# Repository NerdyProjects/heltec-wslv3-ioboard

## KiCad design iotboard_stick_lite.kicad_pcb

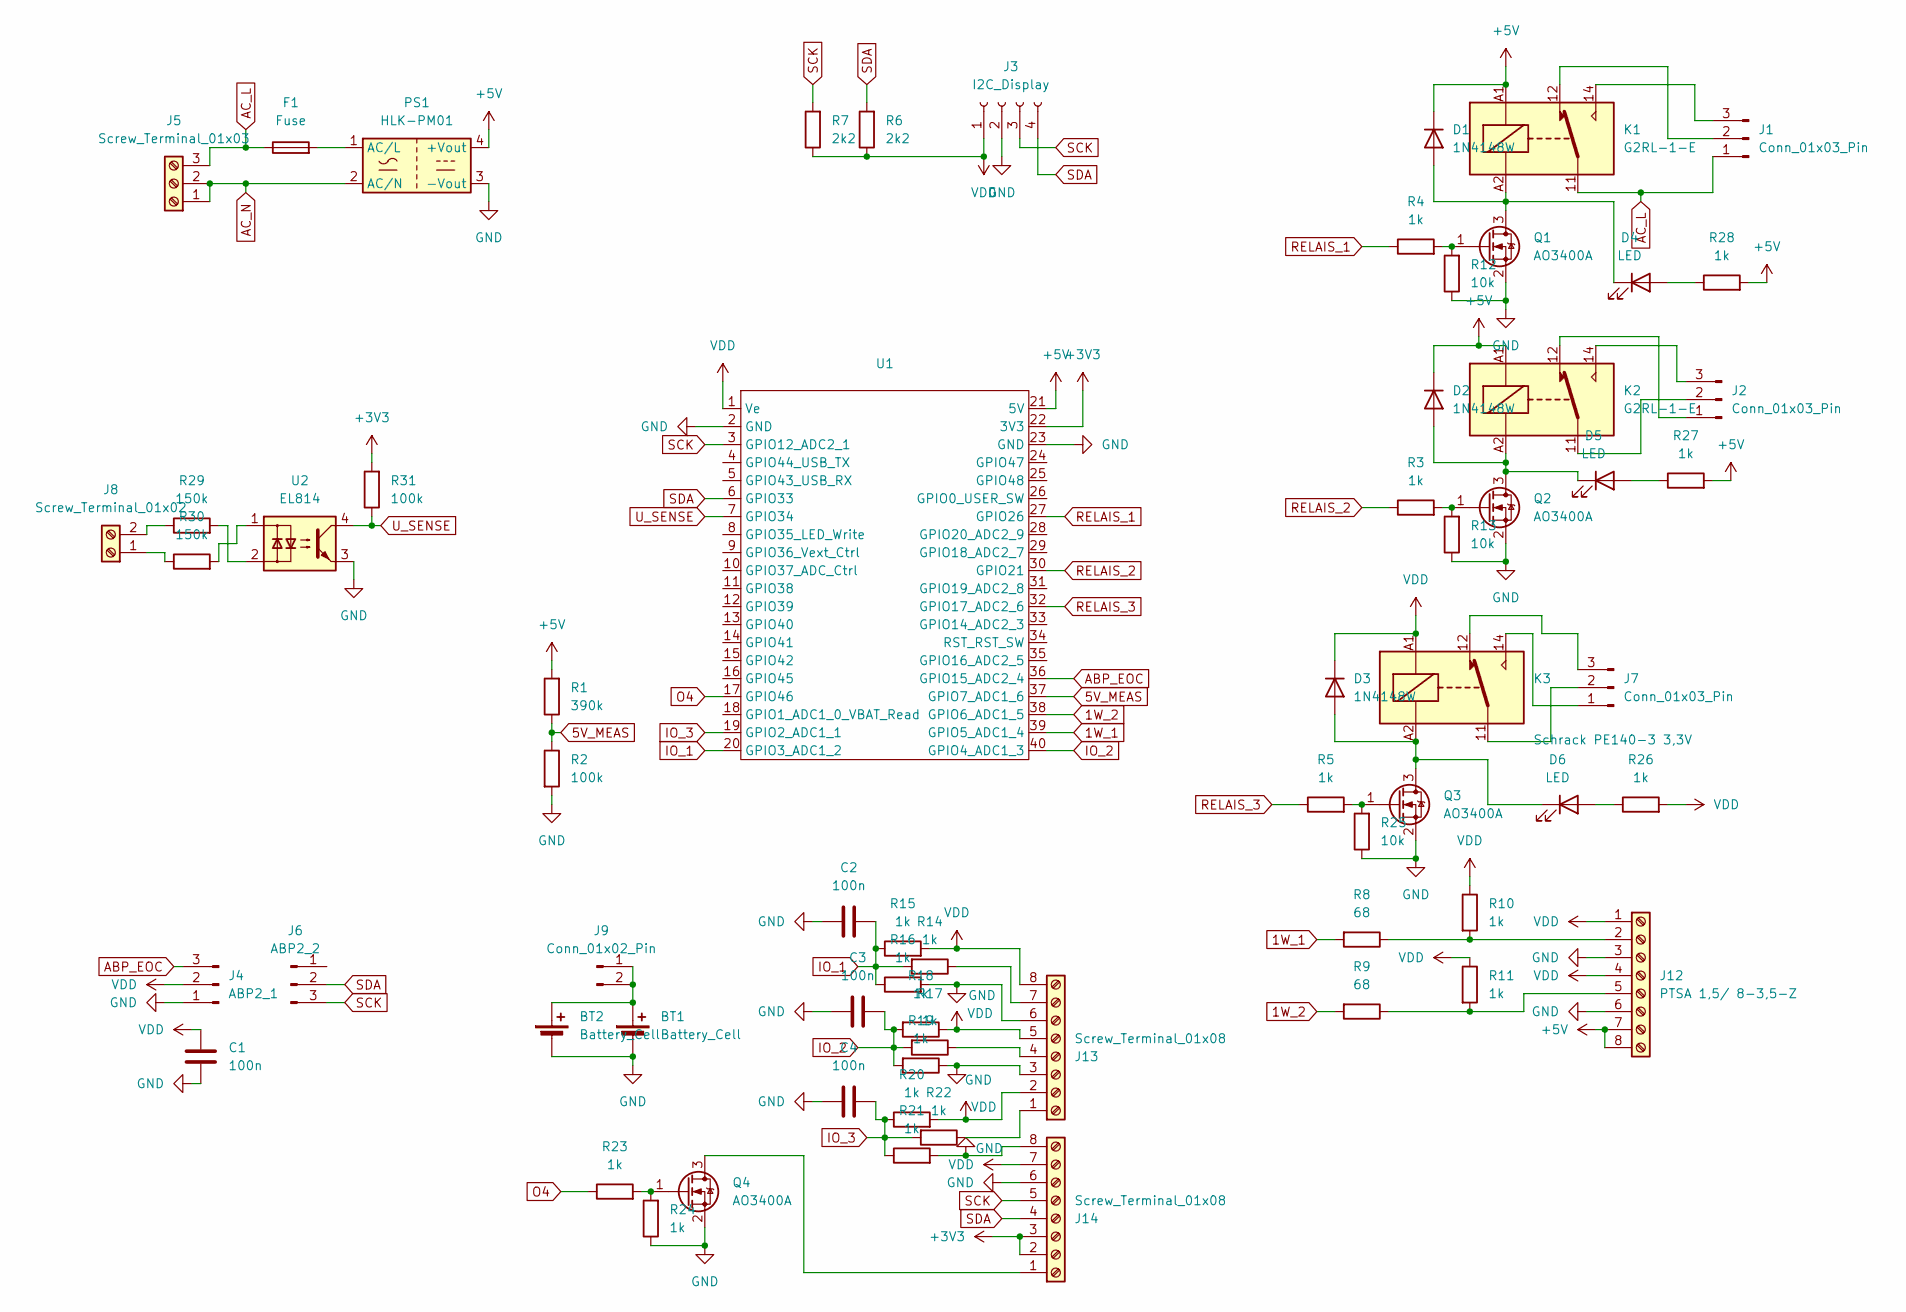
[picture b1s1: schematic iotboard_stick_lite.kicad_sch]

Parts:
BT1, BT2: Battery_Cell; BatteryHolder_MPD_BH-18650-PC2
C1, C2, C3, C4: 100n; C_0805_2012Metric_Pad1.18x1.45mm_HandSolder
D1, D2, D3: 1N4148W; D_SOD-123
D4, D5, D6: LED; LED_D3.0mm
F1: Fuse; R_Axial_DIN0411_L9.9mm_D3.6mm_P7.62mm_Vertical
J1, J2, J7: Conn_01x03_Pin; TerminalBlock_RND_205-00002_1x03_P5.00mm_Horizontal
J3: I2C_Display; PinHeader_1x04_P2.54mm_Vertical
J4: ABP2_1; PinHeader_1x03_P2.54mm_Vertical
J5: Screw_Terminal_01x03; TerminalBlock_RND_205-00002_1x03_P5.00mm_Horizontal
J6: ABP2_2; PinHeader_1x03_P2.54mm_Vertical
J8: Screw_Terminal_01x02; TerminalBlock_4Ucon_1x02_P3.50mm_Horizontal
J9: Conn_01x02_Pin; PinHeader_1x02_P2.54mm_Vertical
J12: PTSA 1,5/ 8-3,5-Z; PHOENIX_1985250
J13, J14: Screw_Terminal_01x08; PHOENIX_1985250
K1, K2: G2RL-1-E; Relay_SPDT_Omron_G2RL-1-E
K3: Schrack PE140-3 3,3V; Relay_SPDT_Finder_32.21-x000
PS1: HLK-PM01; Converter_ACDC_Hi-Link_HLK-PMxx
Q1, Q2, Q3, Q4: AO3400A; SOT-23
R1: 390k; R_0805_2012Metric_Pad1.20x1.40mm_HandSolder
R2, R31: 100k; R_0805_2012Metric_Pad1.20x1.40mm_HandSolder
R3, R4, R5, R10, R11, R14, R15, R16, R17, R18, R19, R20, R21, R22, R23, R24, R26, R27, R28: 1k; R_0805_2012Metric_Pad1.20x1.40mm_HandSolder
R6, R7: 2k2; R_0805_2012Metric_Pad1.20x1.40mm_HandSolder
R8, R9: 68; R_0805_2012Metric_Pad1.20x1.40mm_HandSolder
R12, R13, R25: 10k; R_0805_2012Metric_Pad1.20x1.40mm_HandSolder
R29, R30: 150k; R_1206_3216Metric
U1: Heltec_Wireless_Stick_Lite_V3
U2: EL814; DIP-4_W7.62mm

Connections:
1W_1: R8.2, U1.39 (GPIO5_ADC1_4)
1W_2: R9.2, U1.38 (GPIO6_ADC1_5)
5V_MEAS: R1.1, R2.1, U1.37 (GPIO7_ADC1_6)
+3V3: J14.2, J14.3, R31.2, U1.22 (3V3)
+5V: D1.1 (K), D2.1 (K), J12.7, J12.8, K1.A1, K2.A1, PS1.4 (+Vout), R1.2, R27.2, R28.2, U1.21 (5V)
ABP_EOC: J4.3, U1.36 (GPIO15_ADC2_4)
AC_L: F1.1, J1.1, J5.3, K1.11
AC_N: J5.1, J5.2, PS1.2 (AC/N)
GND: BT1.2 (-), BT2.2 (-), C1.2, C2.1, C3.1, C4.1, J3.2, J4.1, J12.3, J12.6, J13.3, J13.6, J14.6, J14.8, PS1.3 (-Vout), Q1.2 (S), Q2.2 (S), Q3.2 (S), Q4.2 (S), R2.2, R12.1, R13.1, R16.2, R19.1, R21.2, R24.1, R25.1, U1.2 (GND), U1.23 (GND), U2.3
IO_1: C2.2, R14.2, R15.1, R16.1, U1.20 (GPIO3_ADC1_2)
IO_2: C3.2, R17.2, R18.2, R19.2, U1.40 (GPIO4_ADC1_3)
IO_3: C4.2, R20.1, R21.1, R22.2, U1.19 (GPIO2_ADC1_1)
unnamed: BT1.1 (+), BT2.1 (+), J9.1, J9.2
unnamed: D1.2 (A), D4.1 (K), K1.A2, Q1.3 (D)
unnamed: D2.2 (A), D5.1 (K), K2.A2, Q2.3 (D)
unnamed: D3.2 (A), D6.1 (K), K3.A2, Q3.3 (D)
unnamed: D4.2 (A), R28.1
unnamed: D5.2 (A), R27.1
unnamed: D6.2 (A), R26.1
unnamed: J1.2, K1.12
unnamed: J1.3, K1.14
unnamed: J2.1, K2.12
unnamed: J2.2, K2.11
unnamed: J2.3, K2.14
unnamed: J7.1, K3.14
unnamed: J7.2, K3.11
unnamed: J7.3, K3.12
unnamed: J8.1, R30.1
unnamed: J8.2, R29.1
unnamed: J12.2, R8.1, R10.2
unnamed: J12.5, R9.1, R11.2
unnamed: J13.1, R22.1
unnamed: J13.4, R17.1
unnamed: J13.7, R14.1
unnamed: J14.1, Q4.3 (D)
unnamed: F1.2, PS1.1 (AC/L)
unnamed: Q1.1 (G), R4.2, R12.2
unnamed: Q2.1 (G), R3.2, R13.2
unnamed: Q3.1 (G), R5.2, R25.2
unnamed: Q4.1 (G), R23.2, R24.2
unnamed: R29.2, U2.2
unnamed: R30.2, U2.1
O4: R23.1, U1.17 (GPIO46)
RELAIS_1: R4.1, U1.27 (GPIO26)
RELAIS_2: R3.1, U1.30 (GPIO21)
RELAIS_3: R5.1, U1.32 (GPIO17_ADC2_6)
SCK: J3.3, J6.3, J14.5, R7.2, U1.3 (GPIO12_ADC2_1)
SDA: J3.4, J6.2, J14.4, R6.2, U1.6 (GPIO33)
U_SENSE: R31.1, U1.7 (GPIO34), U2.4
VDD: C1.1, D3.1 (K), J3.1, J4.2, J12.1, J12.4, J13.2, J13.5, J13.8, J14.7, K3.A1, R6.1, R7.1, R10.1, R11.1, R15.2, R18.1, R20.2, R26.2, U1.1 (Ve)

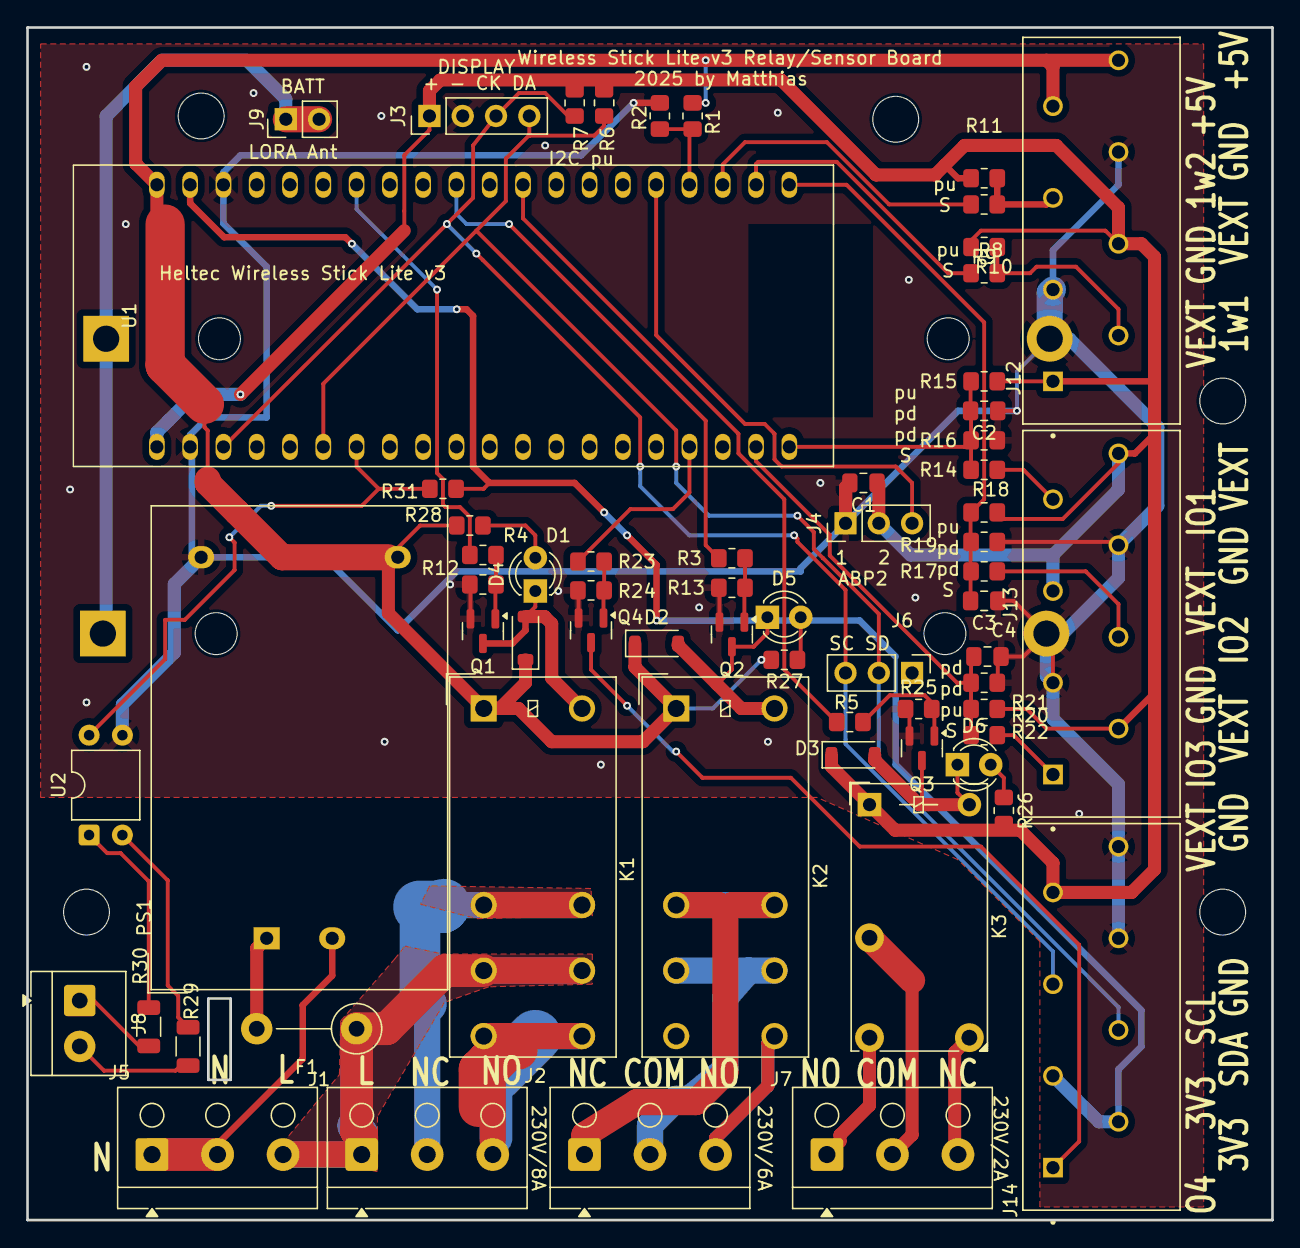
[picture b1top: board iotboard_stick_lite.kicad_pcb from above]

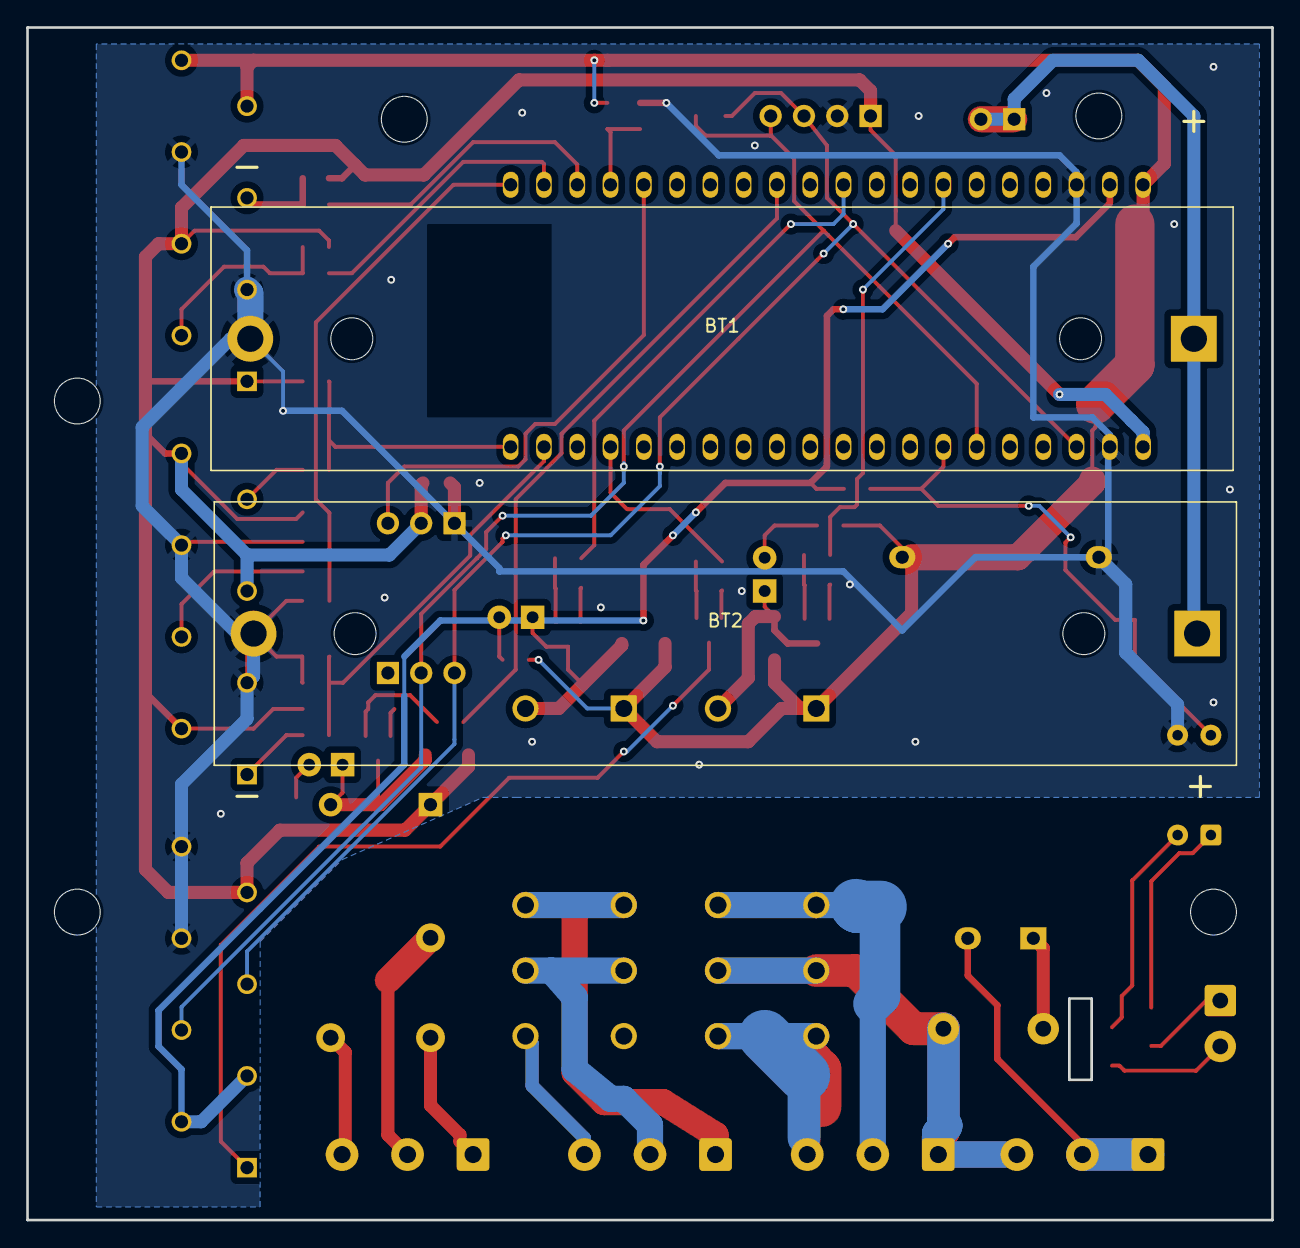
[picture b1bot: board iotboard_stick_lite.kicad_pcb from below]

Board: 2 copper layers, 95.0 x 91.0 mm, 66 parts (2 on the bottom side), 50 nets.

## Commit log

2025-05-09 Initial
